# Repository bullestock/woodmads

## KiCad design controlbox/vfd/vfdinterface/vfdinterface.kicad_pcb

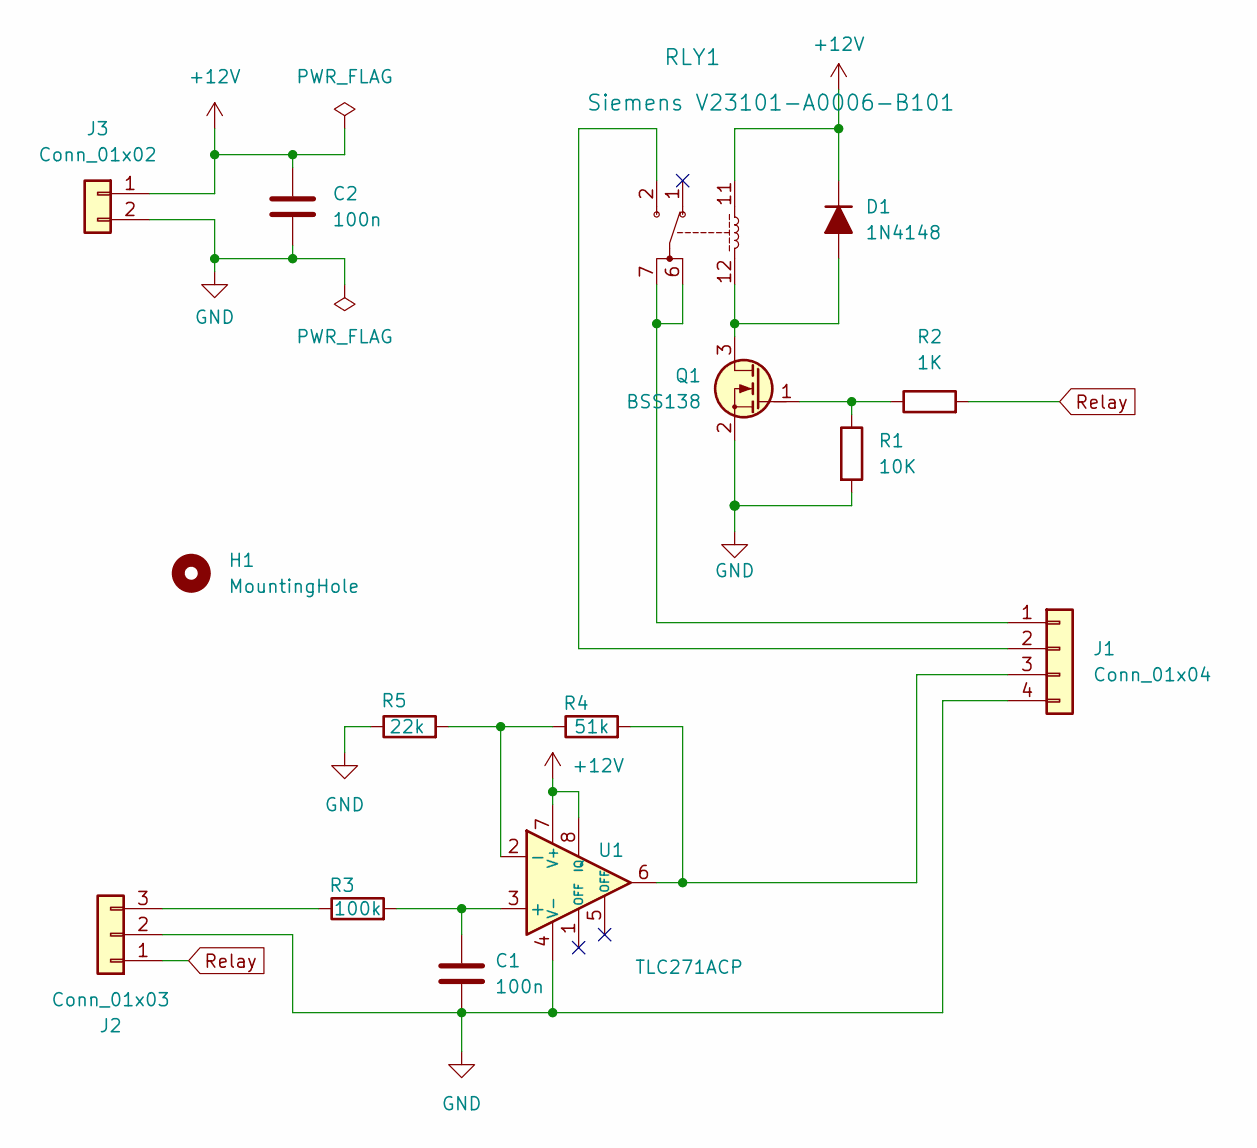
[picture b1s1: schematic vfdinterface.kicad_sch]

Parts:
C1, C2: 100n; C_0603_1608Metric
D1: 1N4148; D_MiniMELF
H1: MountingHole; MountingHole_3.2mm_M3
J1: Conn_01x04; JST_XH_B4B-XH-A_1x04_P2.50mm_Vertical
J2: Conn_01x03; JST_XH_B3B-XH-A_1x03_P2.50mm_Vertical
J3: Conn_01x02; JST_XH_B2B-XH-A_1x02_P2.50mm_Vertical
Q1: BSS138; SOT-23
R1: 10K; R_0603_1608Metric
R2: 1K; R_0603_1608Metric
R3: 100k; R_0603_1608Metric
R4: 51k; R_0603_1608Metric
R5: 22k; R_0603_1608Metric
RLY1: Siemens V23101-A0006-B101; relay_V23101-D0-B
U1: TLC271ACP; DIP-8_W7.62mm

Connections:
+12V: C2.1, D1.1 (K), J3.1, RLY1.11, U1.7 (V+), U1.8 (IQ)
GND: C1.2, C2.2, J1.4, J2.2, J3.2, Q1.2 (S), R1.2, R5.1, U1.4 (V-)
unnamed: D1.2 (A), Q1.3 (D), RLY1.12
unnamed: J1.1, RLY1.6, RLY1.7
unnamed: J1.2, RLY1.2
unnamed: J1.3, R4.2, U1.6
unnamed: J2.3, R3.1
unnamed: Q1.1 (G), R1.1, R2.1
unnamed: C1.1, R3.2, U1.3 (+)
unnamed: R4.1, R5.2, U1.2 (-)
Relay: J2.1, R2.2

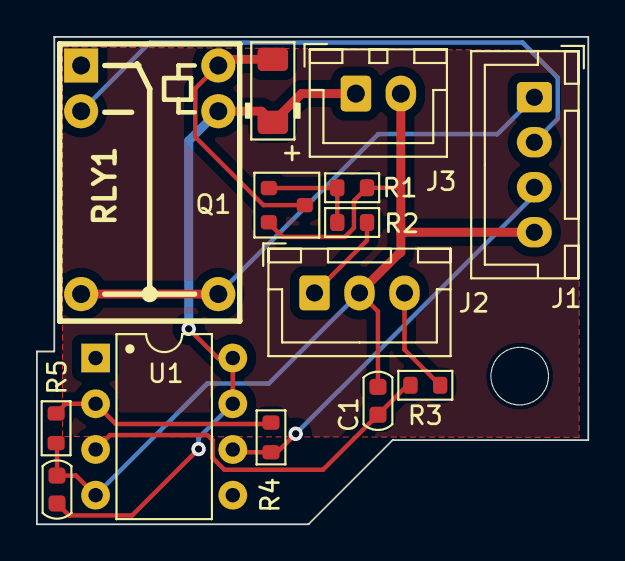
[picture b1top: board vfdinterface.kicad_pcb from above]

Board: 2 copper layers, 30.6 x 27.1 mm, 15 parts (0 on the bottom side), 11 nets.

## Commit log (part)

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2023-04-10 First attempt.
2023-06-08 Box for control panel.
2023-06-10 First print.
2023-06-10 Fix error.
2023-06-10 Front for control panel
2024-01-14 Initial attempt - homing works, but more backoff needed.
2024-01-15 Update.
2024-01-20 Save grblHAL settings. Add controlbox CAD files.
2024-01-20 Update grbl settings.
2024-01-20 Update grbl settings for DM542T set to 2000 pulses/rev.
2024-02-04 Holder for spindle hoses + cable.
2024-02-11 Add VFD interface PCB.
2024-02-11 Place components.
2024-02-11 Route.
2024-02-11 Finish routing.
2024-02-11 Add fills.
2024-02-12 Holder for vise.
2024-02-17 Box for switch for VFD and pump.
2024-03-03 Fix resolution setting.
2024-03-23 Holder for vfdinterface pcb.
2024-03-24 Update resolution.
2024-03-24 Fix opamp gain.
2024-03-24 Move to correct project.
2024-03-30 Change to DIL package.
2024-04-20 Case for thermometer, upper part.
2024-09-21 New design for thermometer box.
2025-04-26 Add stuff.
2025-05-02 Skirt holder for spindle.
2025-05-02 Adapters for hose.
2025-05-03 Add screw holes.
2025-05-03 Convert to press-fit.
2025-06-01 Bottom part with magnets.
2025-06-02 Tweak.
2025-08-02 Ignore.
2025-09-18 Labels for bits.
2025-09-20 New version with fan PSU.
2025-09-21 Save Robin Nano firmware from terjeio.
2025-10-12 For establishing reference point for items mounted in vice.
2025-10-31 More labels.
2025-11-02 Add.
2025-11-08 Add script for configuring grblHAL.
2025-11-16 Set minimum spindle speed to zero.
2025-12-22 Frames for flow counter and thermometer.
